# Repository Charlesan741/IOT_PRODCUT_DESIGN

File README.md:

# IOT_PRODCUT_DESIGN
This is the creation step by step of a IOT product design, using project managment methods and electronic design abilities 
test of add

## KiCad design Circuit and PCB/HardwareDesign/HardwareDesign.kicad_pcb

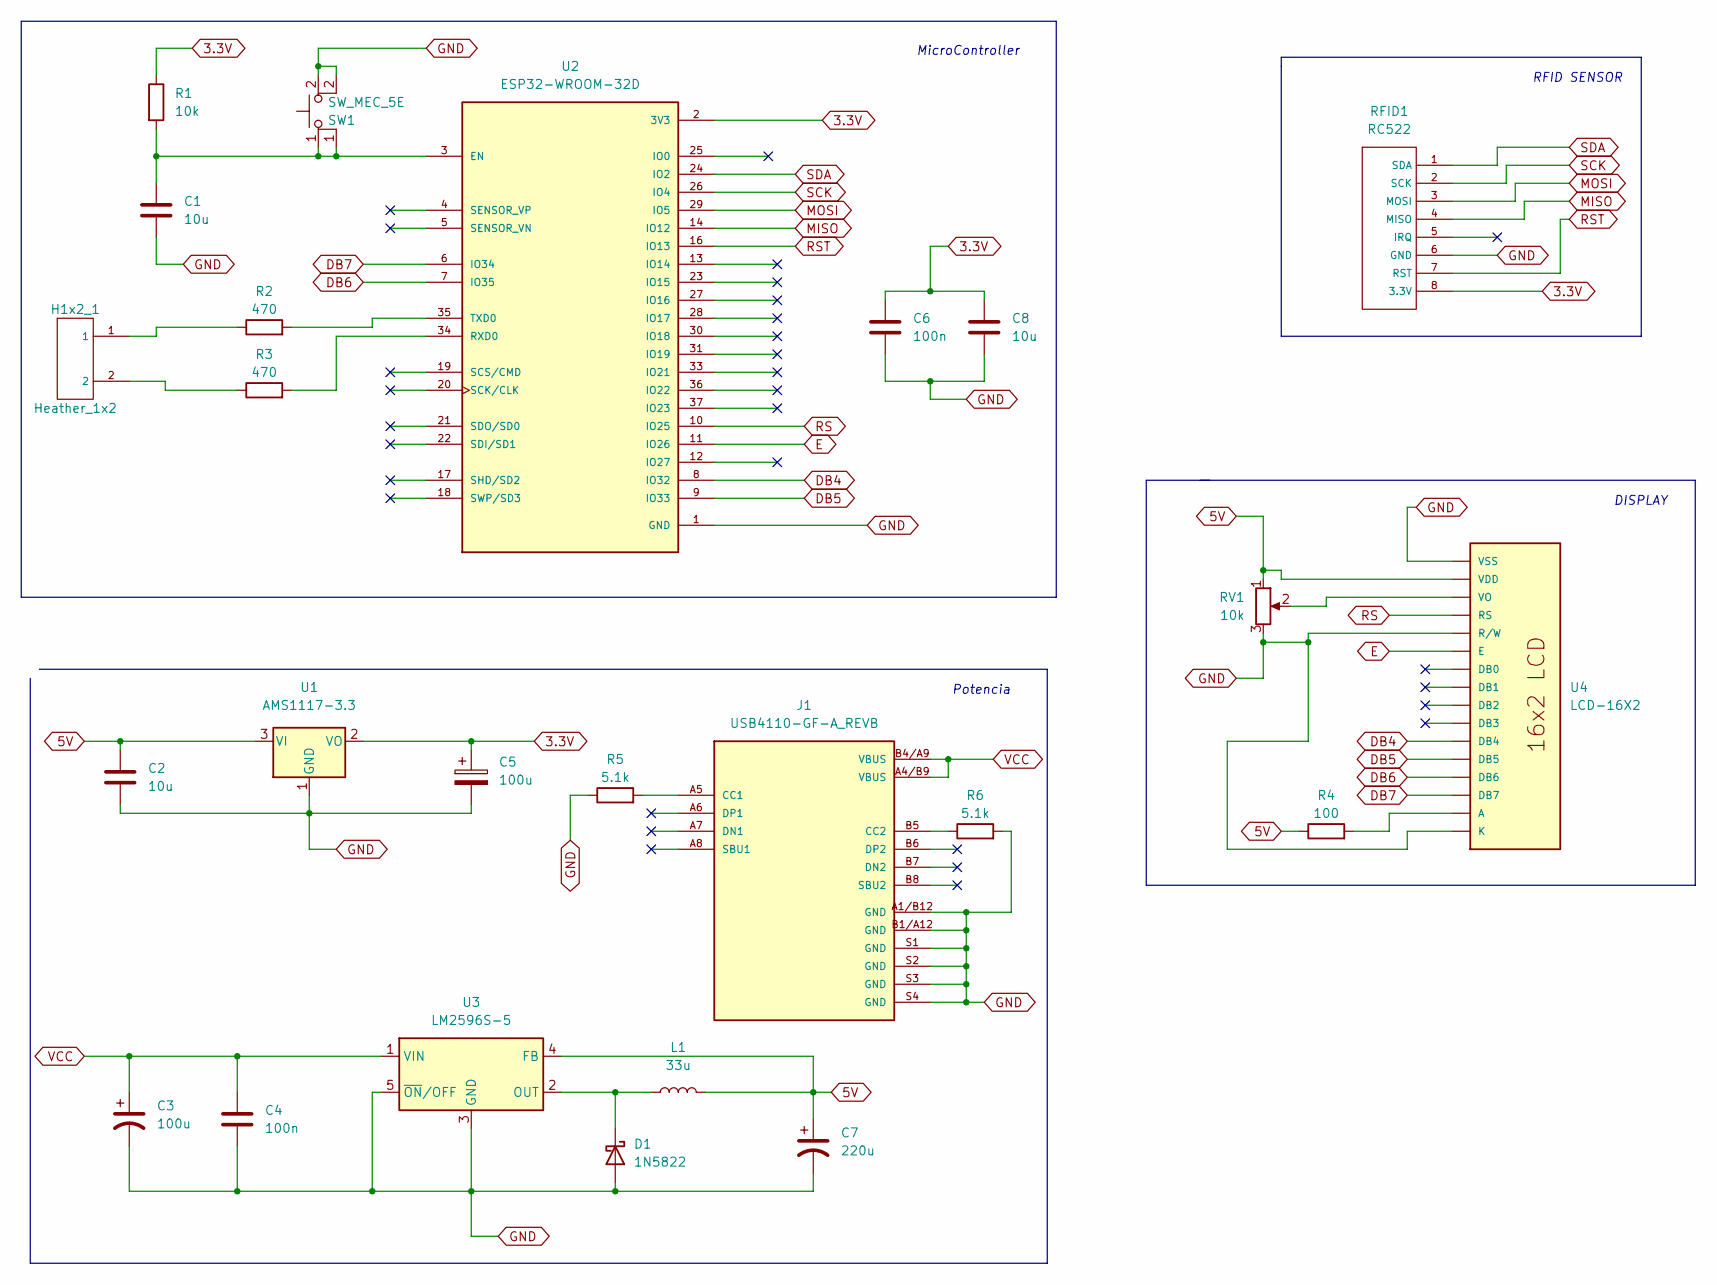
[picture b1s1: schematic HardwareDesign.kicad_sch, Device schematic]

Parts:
C1, C2, C8: 10u; C_0805_2012Metric
C3: 100u; CP_Elec_6.3x5.7
C4, C6: 100n; C_0805_2012Metric
C5: 100u; C_0805_2012Metric
C7: 220u; CP_Elec_6.3x5.7
D1: 1N5822; D_DO-201AD_P15.24mm_Horizontal
H1x2_1: Heather_1x2; header_1x2
J1: USB4110-GF-A_REVB; GCT_USB4110-GF-A_REVB; PARTREV B
L1: 33u; L_10.4x10.4_H4.8
R1: 10k; R_0805_2012Metric
R2, R3: 470; R_0603_1608Metric
R4: 100; R_0603_1608Metric
R5, R6: 5.1k; R_0603_1608Metric
RFID1: RC522; Header_1x8
RV1: 10k; Potenciometer 10k
SW1: SW_MEC_5E; SW_PUSH_6mm_H4.3mm
U1: AMS1117-3.3; SOT-223-3_TabPin2
U2: ESP32-WROOM-32D; MODULE_ESP32-WROOM-32D; PARTREV 1.9
U3: LM2596S-5; TO-263-5_TabPin3
U4: LCD-16X2; Header_1x16

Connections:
3.3V: C5.1, C6.1, C8.1, R1.1, RFID1.8 (3.3V), U1.2 (VO), U2.2 (3V3)
5V: C2.1, C7.1, L1.2, R4.1, RV1.1, U1.3 (VI), U3.4 (FB), U4.2 (VDD)
DB4: U2.8 (IO32), U4.11 (DB4)
DB5: U2.9 (IO33), U4.12 (DB5)
DB6: U2.7 (IO35), U4.13 (DB6)
DB7: U2.6 (IO34), U4.14 (DB7)
E: U2.11 (IO26), U4.6 (E)
GND: C1.2, C2.2, C3.2, C4.2, C5.2, C6.2, C7.2, C8.2, D1.2 (A), J1.A1/B12 (GND), J1.B1/A12 (GND), J1.S1 (GND), J1.S2 (GND), J1.S3 (GND), J1.S4 (GND), R5.1, R6.2, RFID1.6 (GND), RV1.3, SW1.2, U1.1 (GND), U2.1 (GND), U3.3 (GND), U3.5 (~ON/OFF), U4.1 (VSS), U4.5 (R/W), U4.16 (K)
MISO: RFID1.4 (MISO), U2.14 (IO12)
MOSI: RFID1.3 (MOSI), U2.29 (IO5)
unnamed: C1.1, R1.2, SW1.1, U2.3 (EN)
unnamed: D1.1 (K), L1.1, U3.2 (OUT)
unnamed: H1x2_1.1, R2.1
unnamed: H1x2_1.2, R3.1
unnamed: J1.A5 (CC1), R5.2
unnamed: J1.B5 (CC2), R6.1
unnamed: R2.2, U2.35 (TXD0)
unnamed: R3.2, U2.34 (RXD0)
unnamed: R4.2, U4.15 (A)
unnamed: RV1.2, U4.3 (VO)
RS: U2.10 (IO25), U4.4 (RS)
RST: RFID1.7 (RST), U2.16 (IO13)
SCK: RFID1.2 (SCK), U2.26 (IO4)
SDA: RFID1.1 (SDA), U2.24 (IO2)
VCC: C3.1, C4.1, J1.A4/B9 (VBUS), J1.B4/A9 (VBUS), U3.1 (VIN)

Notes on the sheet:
RFID SENSOR
DISPLAY
Potencia
MicroController

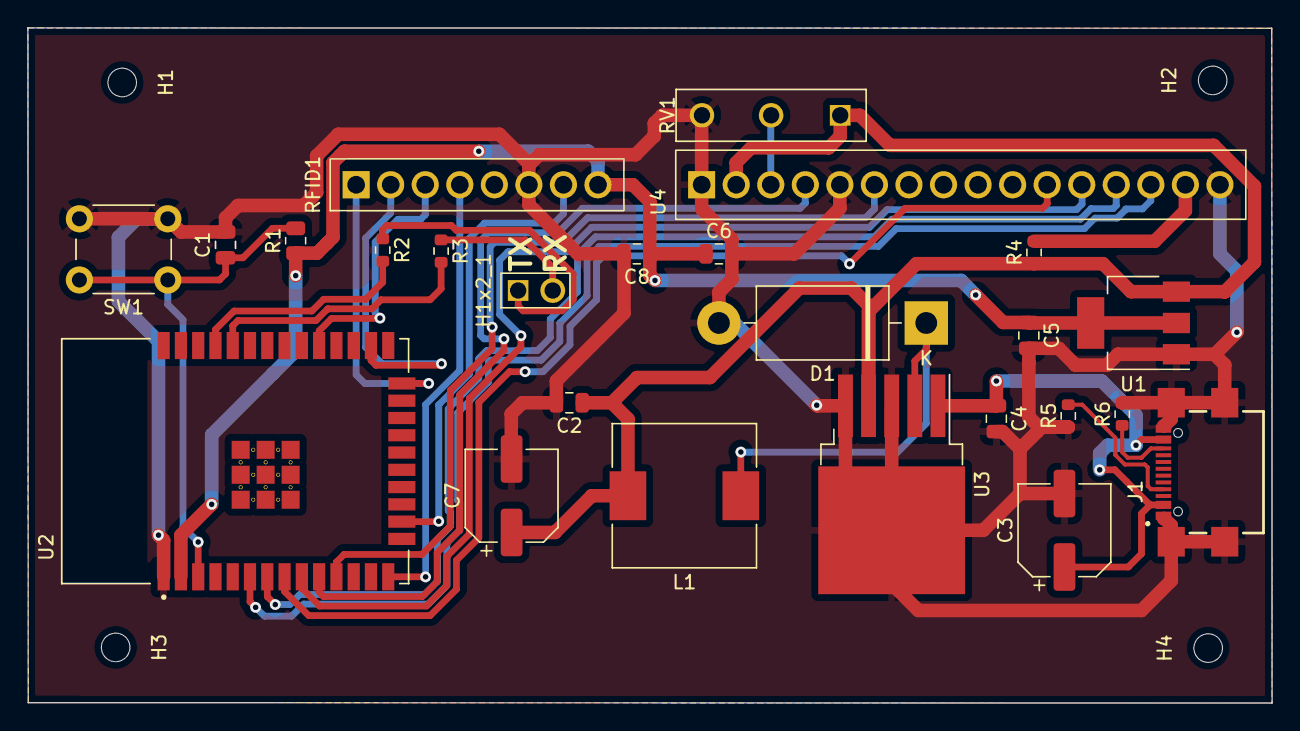
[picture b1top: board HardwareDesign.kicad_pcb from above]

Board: 2 copper layers, 91.5 x 49.6 mm, 29 parts (0 on the bottom side), 25 nets.

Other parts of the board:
H1, H2, H3, H4: MountingHole_2.1mm

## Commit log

2022-10-05 add design files
2022-10-06 documento de requerimientos y presentacion proyecto
2022-10-11 add kicad project files
2022-10-28 add schematic
2022-11-07 PCB design complete
2022-11-16 add USB-C connector
2022-12-02 gerber files
